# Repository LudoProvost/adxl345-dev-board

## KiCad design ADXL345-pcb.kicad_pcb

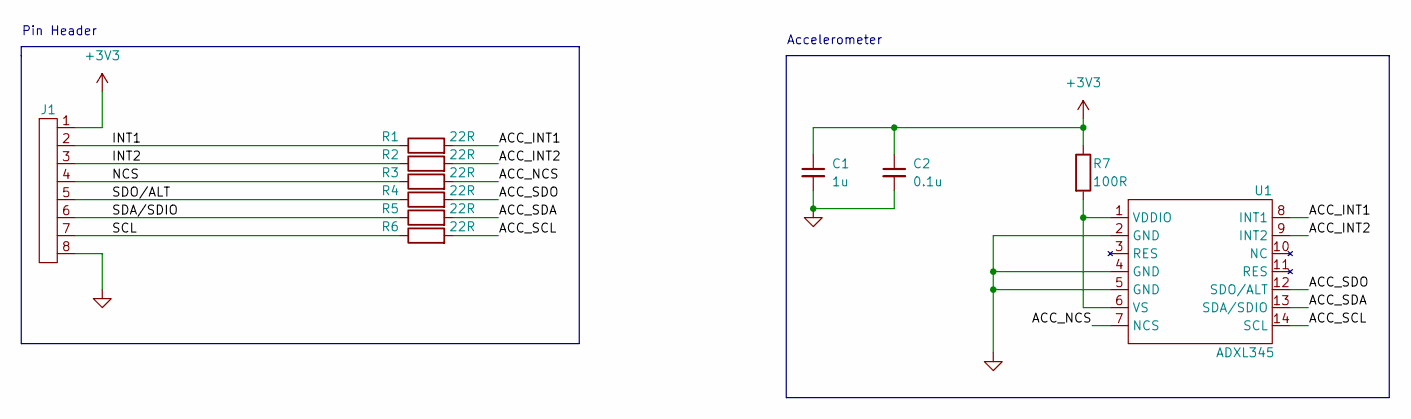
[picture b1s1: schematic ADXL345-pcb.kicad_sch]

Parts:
C1: 1u; C_1206_3216Metric
C2: 0.1u; C_0603_1608Metric
J1: 8_Pin_Header
R1, R2, R3, R4, R5, R6: 22R; R_0603_1608Metric
R7: 100R; R_2010_5025Metric
U1: ADXL345

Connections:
+3V3: C1.1, C2.1, J1.1, R7.1
/ACC_INT1: R1.2, U1.8 (INT1)
/ACC_INT2: R2.2, U1.9 (INT2)
/ACC_NCS: R3.2, U1.7 (NCS)
/ACC_SCL: R6.2, U1.14 (SCL)
/ACC_SDA: R5.2, U1.13 (SDA/SDIO)
/ACC_SDO: R4.2, U1.12 (SDO/ALT)
/INT1: J1.2, R1.1
/INT2: J1.3, R2.1
/NCS: J1.4, R3.1
/SCL: J1.7, R6.1
/SDA/SDIO: J1.6, R5.1
/SDO/ALT: J1.5, R4.1
GND: C1.2, C2.2, J1.8, U1.2 (GND), U1.4 (GND), U1.5 (GND)
unnamed: R7.2, U1.1 (VDDIO), U1.6 (VS)

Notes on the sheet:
Pin Header
Accelerometer

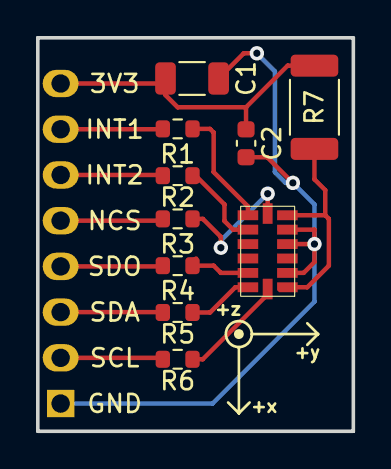
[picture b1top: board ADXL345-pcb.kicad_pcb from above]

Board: 2 copper layers, 17.5 x 21.9 mm, 11 parts (0 on the bottom side), 15 nets.
